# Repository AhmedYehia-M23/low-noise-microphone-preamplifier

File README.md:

# Low-Noise Electret Microphone Preamplifier

A 5 V single-supply electret microphone preamplifier designed in KiCad 10. The production PCB uses an **Analog Devices AD8656ARMZ** dual op-amp (MSOP-8), adjustable non-inverting gain targeting approximately **30–40 dB**, and RC high-pass and low-pass filtering.

**Status:** PCB design finalized and released for fabrication; assembly and bench testing remain pending. The repository contains user-run **AD8656 LTspice simulations** and separately archived results from an earlier OPA165x-based revision.

## Project files

- [PCB assembly BOM](hardware/BOM.md) ([CSV](hardware/BOM.csv))
- [Editable KiCad schematic](hardware/kicad/Microphone.kicad_sch)
- [Editable KiCad PCB](hardware/kicad/Microphone.kicad_pcb)
- [KiCad project settings](hardware/kicad/Microphone.kicad_pro)
- [AD8656 LTspice schematic](simulation/ltspice/Microphone_Preamplifier_AD8656.asc)
- [Earlier OPA165x LTspice schematic](simulation/ltspice/Microphone_Preamplifier_OPA165x.asc)
- [LTspice setup notes](simulation/ltspice/README.md)
- [Noise analysis notes](docs/noise-analysis.md) — resistor noise estimates and final-device measurement plan

## Project status

| Stage | Status |
| --- | --- |
| Circuit and PCB design | Complete |
| KiCad DRC | **0 errors, 0 warnings, 0 unconnected items, 0 schematic parity violations** on the final local design |
| PCB fabrication | Design released for fabrication |
| PCB assembly | Pending; components will be soldered by hand |
| LTspice analyses | Passed for the earlier OPA165x-based simulation |
| AD8656 simulation | User-run AC, transient and noise results documented; not independently rerun |
| Bench gain, bandwidth, noise and supply-current measurements | Pending |

The files in `hardware/kicad/` are the final production-source revision. Gerbers and drill exports are not included in this repository.

## Hardware specifications

| Parameter | Final design |
| --- | --- |
| Supply | 5 V DC |
| Microphone | EKULIT EMY-6027P/N-R-42 electret capsule |
| Op-amp | **AD8656ARMZ** (dual, MSOP-8; KiCad value `AD8656`) |
| Gain | Adjustable; nominal target approximately 30–40 dB |
| High-pass network | 100 nF / 47 kΩ; nominal corner approximately 33.9 Hz |
| Low-pass network | 330 Ω / 27 nF; nominal corner approximately 17.9 kHz |
| Power switch | SPDT slide switch, SS ESP101 / ESP1010 footprint |
| Power indicator | Green 1206 LED (`D1`) and 2.2 kΩ series resistor (`R9`) |
| PCB | 2 layers, approximately 60.06 × 40.03 mm, 1.6 mm FR-4, 1 oz copper |
| Layout | Bottom-layer GND plane, 0603 passives, through-hole connectors and test points |

The nominal RC corner frequencies are **component-value calculations**, not measured bandwidth for the AD8656 hardware.

## Signal path

**Electret microphone → bias / AC coupling → AD8656 non-inverting gain stage → RC low-pass filter → output coupling → audio output**

The other amplifier in the dual AD8656 buffers the mid-supply reference.

### Microphone input

The electret capsule is biased through **R3 = 2.2 kΩ**. The microphone signal passes through **C4 = 100 nF** into the amplifier input network; **R4 = 47 kΩ** sets the nominal high-pass corner.

```text
f_HP = 1 / (2π × 47 kΩ × 100 nF) ≈ 33.9 Hz
```

The microphone's project-local footprint is in `hardware/kicad/AudioPreamp.pretty/`.

### Mid-supply reference

A **10 kΩ / 10 kΩ** divider (`R1`, `R2`) derives approximately **2.5 V** from the 5 V supply. **C3 = 10 µF** filters the divider node; the second AD8656 channel buffers it as `VREF`.

### Variable gain

The non-inverting amplifier uses:

- **R5 = 22 kΩ**
- **R6 = 220 Ω**
- **RV1 = 500 Ω** adjustable potentiometer

The idealized gain is:

$$
A_v = 1 + \frac{R_5}{R_6 + R_{V1}}
$$

The gain-setting network targets approximately **30–40 dB**, depending on the potentiometer setting. This is a **design target**, not a measured AD8656 gain result.

### Low-pass and output coupling

**R7 = 330 Ω** and **C5 = 27 nF** form the nominal low-pass filter:

```text
f_LP = 1 / (2π × 330 Ω × 27 nF) ≈ 17.9 kHz
```

**C6 = 4.7 µF** AC-couples the signal to `AUDIO_OUT`; **R8 = 100 kΩ** provides a DC reference at the output.

### Power input and indication

The incoming **5 V** supply is controlled by the on-board **SPDT slide switch (`SW1`)**. A **green 1206 LED (`D1`)** with a **2.2 kΩ series resistor (`R9`)** indicates power.

Power bypassing uses **C1 = 100 nF** and **C2 = 10 µF**; the reference divider is filtered with **C3 = 10 µF**.

## PCB design

The two-layer board includes:

- AD8656 in **MSOP-8, 0.65 mm pitch**
- 0603 resistor/capacitor footprints and a 1206 power LED
- Through-hole electret microphone and adjustable potentiometer
- Screw-terminal connections for power and audio output
- Through-hole SPDT power switch, using the project-local `SW_ESP1010_SPDT_Vertical` footprint
- Bottom-layer ground plane
- Test points for `VREF`, `AMP_OUT`, `LPF_OUT`, `AUDIO_OUT` and GND

The final board was checked in KiCad with **zero DRC errors, warnings, unconnected items and schematic-parity violations** before manufacturing export.

### KiCad schematic

[View the full-resolution schematic](docs/kicad/Microphone.svg)

The editable KiCad source files above contain the final PCB revision. The 3D previews show the final PCB layout; footprints without an associated 3D component model may appear unpopulated.

### Routed PCB layout

### Angled 3D view

## LTspice simulations

### 1 kHz transient response

*AD8656 LTspice transient simulation at 1 kHz (`Rpot=1 Ω`, `I1 = SINE(250u 1u 1k)`). Separate scales show approximately 4.2 mVpp input (`V(VBIAS,VREF)`) and 420 mVpp output (`V(AUDIO_OUT)`), corresponding to approximately 100 V/V (40 dB) simulated gain. The plot does not establish measured hardware performance or total harmonic distortion.*

### AC amplifier-stage gain — maximum setting

*User-run LTspice AC analysis with `Rpot=1 Ω`. Trace: `V(n001,vref)/V(vbias,vref)`, displayed by LTspice in dB. The simulated gain at 1 kHz is approximately **40.05 dB**, consistent with `1 + 22 kΩ / (220 Ω + 1 Ω)`. This is amplifier-stage gain, not the complete microphone-to-output frequency response or a physical measurement.*

### Full signal-path frequency response — 30 dB setting

*User-run LTspice AC sweep with `Rpot=500 Ω`. Trace: `V(audio_out)/V(mic_out)`, shown in dB. The plot shows a band-pass response with approximately **30 dB midband gain**, including both the low- and high-frequency roll-offs. At the 1 kHz gain of **29.5233 dB**, the user-run `.meas AC` results place the approximately −3 dB threshold at **26.5132 dB**, crossing at **30.8214 Hz** and **19,702.8 Hz (19.70 kHz)**. These cutoffs are relative to the 1 kHz gain, not necessarily the absolute passband peak. This is simulated, not hardware-measured, performance.*

### Stepped AC response — adjustable gain

*User-run LTspice AC analysis with `.step param Rpot list 1 179 500`. The green, blue, and red solid curves correspond to approximately **40 dB (1 Ω)**, **35 dB (179 Ω)**, and **30 dB (500 Ω)** midband gain, respectively. Dotted curves show phase; this is the simulated full signal-path response (`V(audio_out)/V(mic_out)`), not physical measurement data.*

### Stepped transient response — three gain settings

*User-run 1 kHz LTspice transient simulation with `I1 = SINE(250u 1u 1k)` and `.step param Rpot list 1 179 500`. The green (1 Ω), blue (179 Ω), and red (500 Ω) traces show approximately **420 mVpp**, **235 mVpp**, and **130 mVpp** at `V(audio_out)`, respectively. Values are approximate readings from the screenshot, not calibrated measurements or distortion results.*

The [AD8656 simulation schematic](simulation/ltspice/Microphone_Preamplifier_AD8656.asc) contains the revised op-amp stages, a **1 kHz sine-wave stimulus** and a clean default **30 dB AC sweep** with gain and cutoff-frequency measurements. Other analysis configurations are documented in the [LTspice setup notes](simulation/ltspice/README.md). It references the external `ad8656.cir` model. The vendor model is not included in the repository. The plots here document user-run LTspice simulations, not independently repeated simulations or physical measurements. The switch and LED are not represented in this analog signal-path simulation.

The [earlier OPA165x schematic](simulation/ltspice/Microphone_Preamplifier_OPA165x.asc) is retained as a record of the original analog-stage development. Its results are historical and must not be attributed to the final AD8656 design.

The previous model passed:

- Operating-point analysis (`.op`)
- Transient analysis
- Stepped transient analysis
- Stepped AC analysis

Previously simulated gain points were approximately **30 / 35 / 40 dB**. At the ~30 dB setting, the previous model showed approximate −3 dB frequencies of **33.9 Hz and 17.8 kHz**. **These are historical OPA165x-model results, not validated AD8656 performance.**

The original results are retained in [`simulation/ltspice/`](simulation/ltspice/) and the repository history, not as current hardware validation.

## Noise and measurement plan

### Simulated output-noise spectral density — 30 dB setting

*User-run LTspice `.noise V(audio_out) I1 dec 100 20 20k` analysis with `Rpot=500 Ω`. The plotted `V(onoise)` is output-noise **amplitude spectral density** in V/√Hz over 20 Hz–20 kHz. It represents the circuit and SPICE model as configured, with an idealized microphone current-source stimulus; it does **not** include the real electret capsule's complete self-noise, and is not itself an integrated RMS noise figure or hardware measurement.*

**Integrated simulated output noise (20 Hz–20 kHz): 31.88 µV RMS**, using `Rpot=500 Ω`. The user-reported LTspice measurement was `.meas NOISE Output_Noise_RMS INTEG V(onoise) FROM=20 TO=20k`, returning `3.18777e-05 V RMS`. This is a simulation result from the configured circuit and AD8656 macro-model, **not a measurement of the real microphone or assembled PCB**.

The final AD8656 implementation has **no published measured noise figure**. Device-level noise specifications and resistor thermal-noise estimates should not be presented as total system noise. The [noise analysis notes](docs/noise-analysis.md) distinguish the earlier OPA1652 reference values from the AD8656 hardware and outline the planned measurements.

After assembly, the planned checks are:

1. Power-rail voltage, polarity, reference voltage and supply current
2. Correct power-switch and LED operation
3. Signal-chain continuity and adjustable gain
4. Frequency response, output swing and clipping
5. Output noise and sensitivity to supply/interference conditions

No bench-tested gain, noise or bandwidth claims are made yet.

## Repository layout

```text
.
├── README.md
├── .gitignore
├── .gitattributes
├── hardware/
│   ├── BOM.md
│   ├── BOM.csv
│   └── kicad/
│       ├── Microphone.kicad_pro
│       ├── Microphone.kicad_sch
│       ├── Microphone.kicad_pcb
│       ├── fp-lib-table
│       └── AudioPreamp.pretty/
│           ├── Microphone_EKULIT_EMY-6027PNR-42.kicad_mod
│           └── SW_ESP1010_SPDT_Vertical.kicad_mod
├── simulation/
│   └── ltspice/
│       ├── Microphone_Preamplifier_AD8656.asc
│       ├── Microphone_Preamplifier_OPA165x.asc
│       └── README.md
└── docs/
    ├── noise-analysis.md
    ├── kicad/
    └── ltspice/
```

## Third-party attribution

- **Analog Devices, Inc.** — manufacturer of the AD8656 operational amplifier and copyright holder of the AD8656 SPICE macro-model (© 2010, 2012 Analog Devices, Inc.). See the [official AD8656 product page](https://www.analog.com/en/products/ad8656.html) for the datasheet and model.
- The Analog Devices SPICE macro-model is **not redistributed** in this repository. It is subject to [Analog Devices' SPICE model license](https://www.analog.com/en/license/spice-models.html); users must obtain it directly from the manufacturer and follow the applicable terms.
- This is an independent electronics project and is **not affiliated with or endorsed by Analog Devices**.

## Open the project

1. Install KiCad 10 (or a compatible newer version).
2. Download or clone this repository.
3. Open `hardware/kicad/Microphone.kicad_pro`.

The microphone and power-switch footprints are stored locally and referenced through the `AudioPreamp.pretty` footprint library. Standard symbols, footprints and 3D models come from the normal KiCad installation.

Temporary backups, KiCad caches, generated manufacturing exports and LTspice waveform files are intentionally excluded from Git.

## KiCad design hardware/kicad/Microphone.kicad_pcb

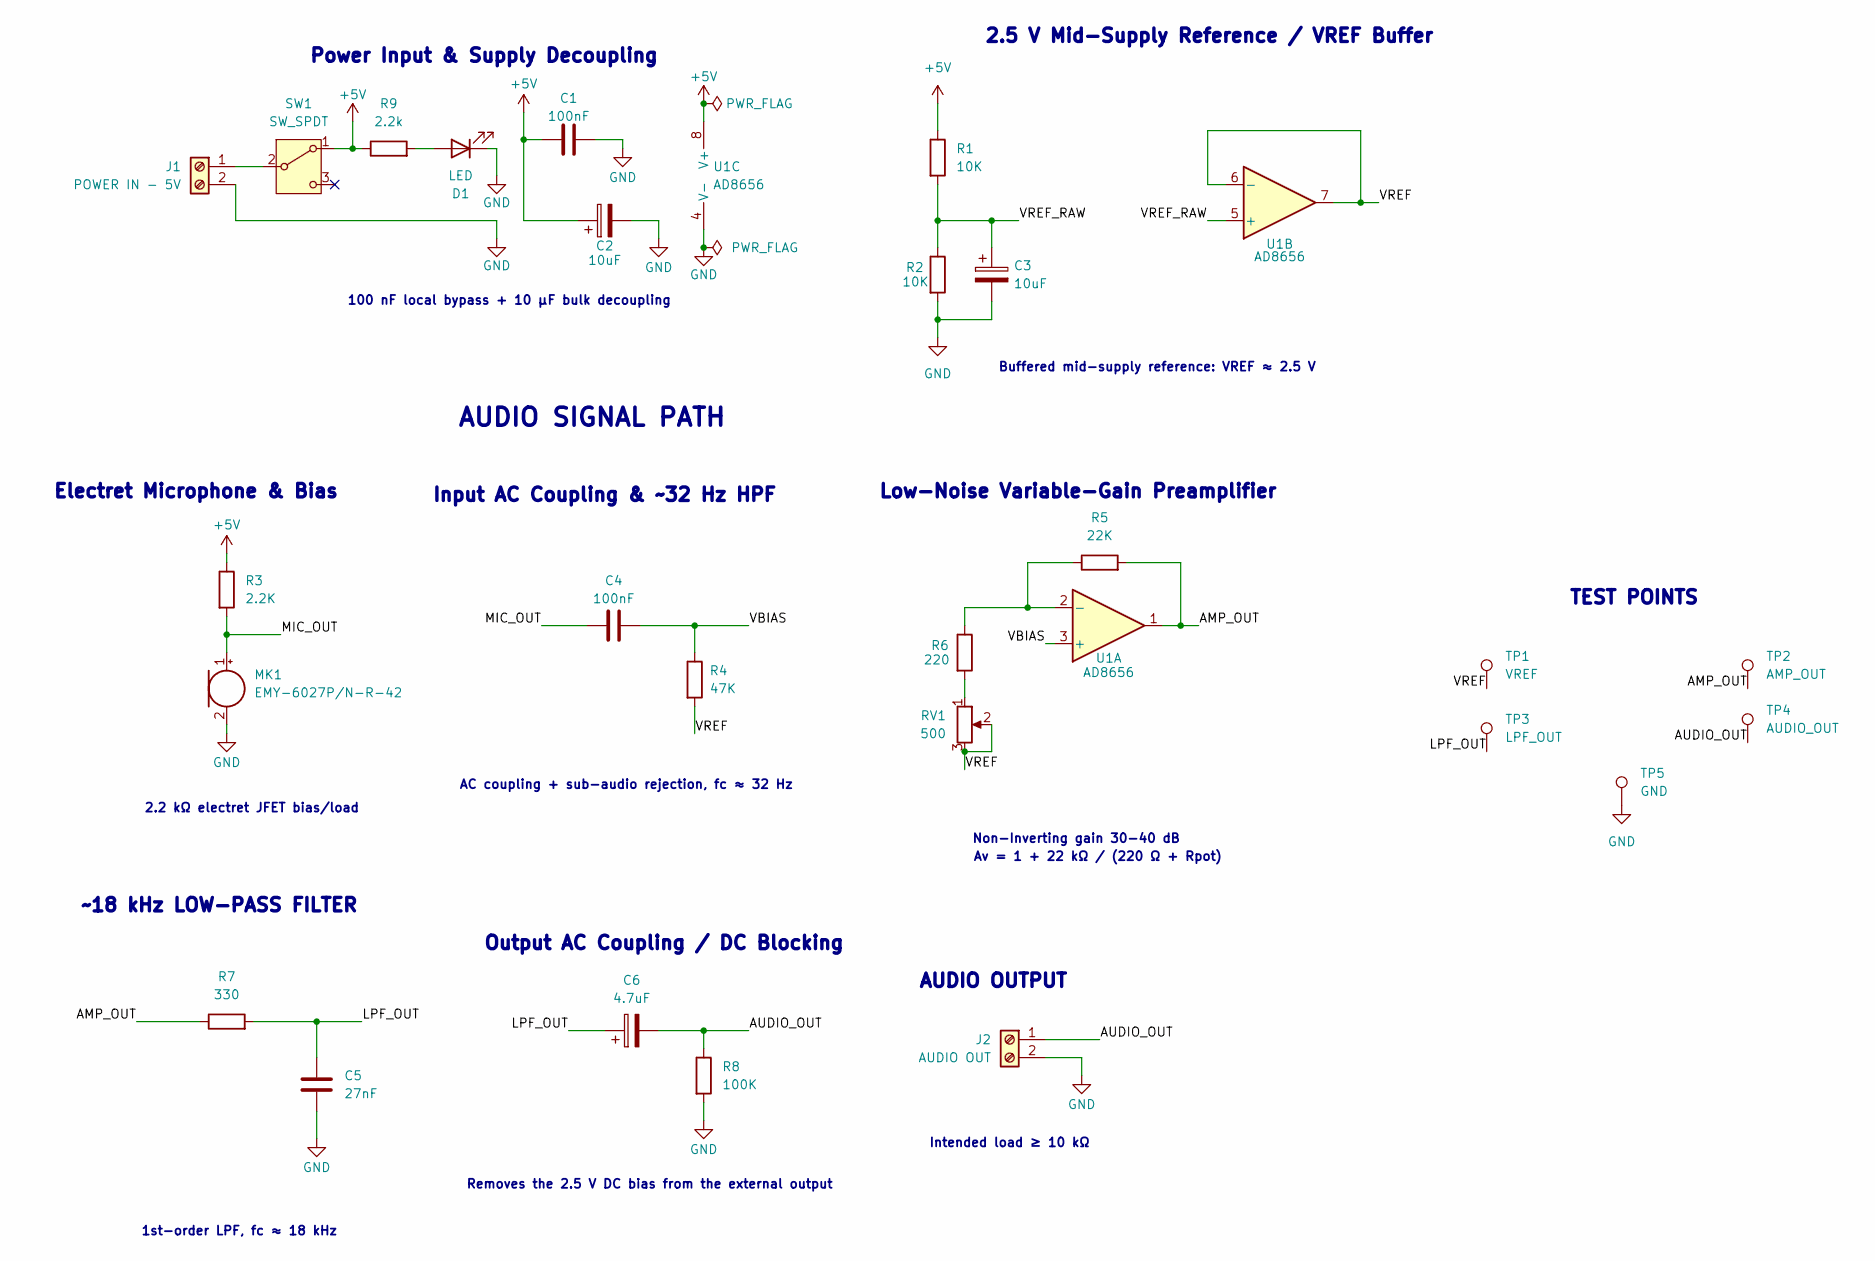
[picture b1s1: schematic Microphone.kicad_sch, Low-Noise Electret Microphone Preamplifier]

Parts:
C1, C4: 100nF; C_0603_1608Metric_Pad1.08x0.95mm_HandSolder
C2, C3: 10uF; CP_Elec_5x5.4
C5: 27nF; C_0603_1608Metric_Pad1.08x0.95mm_HandSolder
C6: 4.7uF; CP_Elec_4x5.8
D1: LED; LED_1206_3216Metric
J1: POWER IN - 5V; TerminalBlock_Phoenix_MKDS-1,5-2-5.08_1x02_P5.08mm_Horizont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
J2: AUDIO OUT; TerminalBlock_Phoenix_MKDS-1,5-2-5.08_1x02_P5.08mm_Horizont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
MK1: EMY-6027P/N-R-42; Microphone_EKULIT_EMY-6027PNR-42
R1, R2: 10K; R_0603_1608Metric_Pad0.98x0.95mm_HandSolder
R3: 2.2K; R_0603_1608Metric_Pad0.98x0.95mm_HandSolder
R4: 47K; R_0603_1608Metric_Pad0.98x0.95mm_HandSolder
R5: 22K; R_0603_1608Metric_Pad0.98x0.95mm_HandSolder
R6: 220; R_0603_1608Metric_Pad0.98x0.95mm_HandSolder
R7: 330; R_0603_1608Metric_Pad0.98x0.95mm_HandSolder
R8: 100K; R_0603_1608Metric_Pad0.98x0.95mm_HandSolder
R9: 2.2k; R_0603_1608Metric_Pad0.98x0.95mm_HandSolder
RV1: 500; Potentiometer_Piher_PT-10-H01_Horizontal
SW1: SW_SPDT; SW_ESP1010_SPDT_Vertical
TP1: VREF; TestPoint_THTPad_D2.0mm_Drill1.0mm
TP2: AMP_OUT; TestPoint_THTPad_D2.0mm_Drill1.0mm
TP3: LPF_OUT; TestPoint_THTPad_D2.0mm_Drill1.0mm
TP4: AUDIO_OUT; TestPoint_THTPad_D2.0mm_Drill1.0mm
TP5: GND; TestPoint_THTPad_D2.0mm_Drill1.0mm
U1: AD8656; MSOP-8_3x3mm_P0.65mm

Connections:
+5V: C1.1, C2.1, R1.1, R3.1, R9.1, SW1.1 (A), U1.8 (V+)
/AMP_OUT: R5.2, R7.1, TP2.1 (1_1), U1.1
/AUDIO_OUT: C6.2, J2.1, R8.1, TP4.1 (1_1)
/LPF_OUT: C5.1, C6.1, R7.2, TP3.1 (1_1)
/MIC_OUT: C4.2, MK1.1 (+), R3.2
/VBIAS: C4.1, R4.1, U1.3 (+)
/VREF: R4.2, RV1.2, RV1.3, TP1.1 (1_1), U1.6 (-), U1.7
/VREF_RAW: C3.1, R1.2, R2.1, U1.5 (+)
GND: C1.2, C2.2, C3.2, C5.2, D1.1 (K), J1.2, J2.2, MK1.2 (-), R2.2, R8.2, TP5.1 (1_1), U1.4 (V-)
unnamed: D1.2 (A), R9.2
unnamed: J1.1, SW1.2 (B)
unnamed: R6.2, RV1.1
unnamed: R5.1, R6.1, U1.2 (-)

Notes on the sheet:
AUDIO SIGNAL PATH
1st-order LPF, fc ≈ 18 kHz
AC coupling + sub-audio rejection, fc ≈ 32 Hz
100 nF local bypass + 10 µF bulk decoupling
Low-Noise Variable-Gain Preamplifier
Input AC Coupling & ~32 Hz HPF
Non-Inverting gain 30-40 dB
Buffered mid-supply reference: VREF ≈ 2.5 V
2.5 V Mid-Supply Reference / VREF Buffer
Output AC Coupling / DC Blocking
Electret Microphone & Bias
TEST POINTS
2.2 kΩ electret JFET bias/load
Power Input & Supply Decoupling
AUDIO OUTPUT
Intended load ≥ 10 kΩ
~18 kHz LOW-PASS FILTER
Av = 1 + 22 kΩ / (220 Ω + Rpot)
Removes the 2.5 V DC bias from the external output

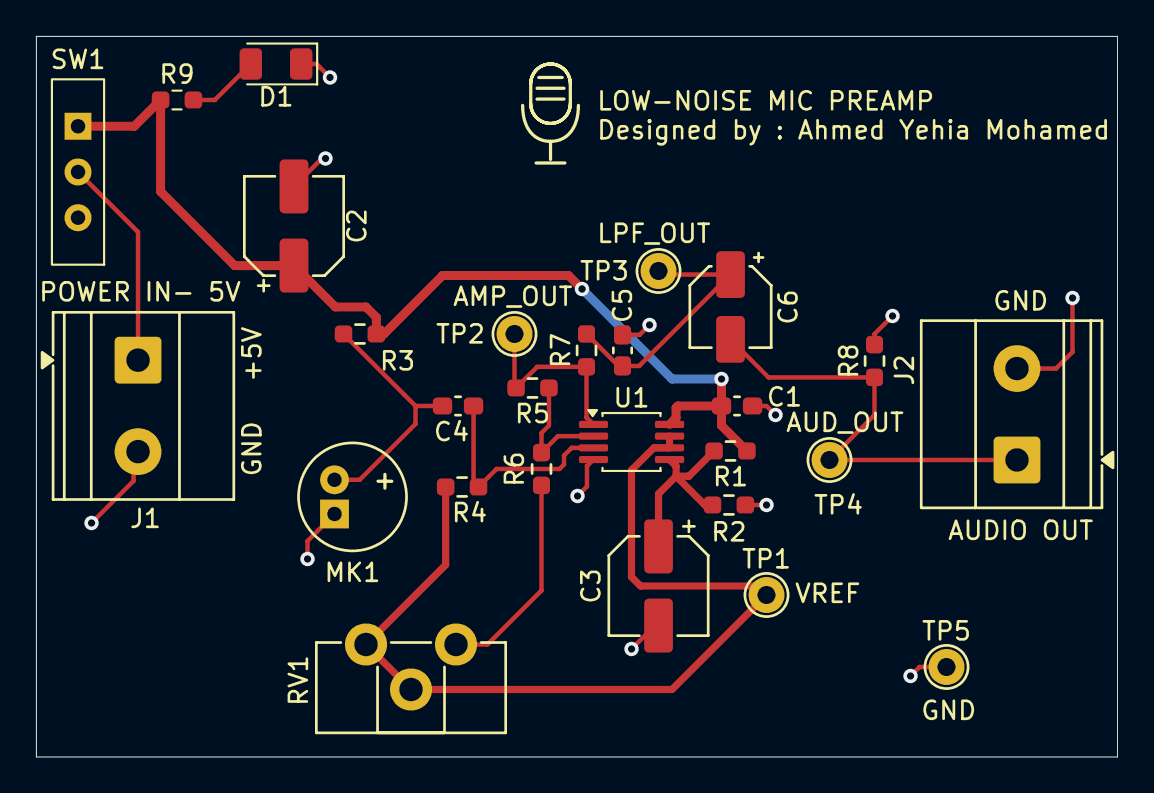
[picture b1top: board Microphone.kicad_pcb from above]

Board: 2 copper layers, 60.1 x 40.0 mm, 27 parts (0 on the bottom side), 13 nets.

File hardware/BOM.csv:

Category,References,Quantity,Value / specification,KiCad footprint,Function,Assembly / verification notes
Resistor,R1 R2,2,10 kΩ,Resistor_SMD:R_0603_1608Metric_Pad0.98x0.95mm_HandSolder,Mid-supply divider,0603; tolerance and power rating not specified in KiCad
Resistor,R3 R9,2,2.2 kΩ,Resistor_SMD:R_0603_1608Metric_Pad0.98x0.95mm_HandSolder,Microphone bias and LED limiting,0603; R9 is the LED series resistor
Resistor,R4,1,47 kΩ,Resistor_SMD:R_0603_1608Metric_Pad0.98x0.95mm_HandSolder,Amplifier input bias,0603
Resistor,R5,1,22 kΩ,Resistor_SMD:R_0603_1608Metric_Pad0.98x0.95mm_HandSolder,Gain feedback,0603
Resistor,R6,1,220 Ω,Resistor_SMD:R_0603_1608Metric_Pad0.98x0.95mm_HandSolder,Gain-setting resistor,0603
Resistor,R7,1,330 Ω,Resistor_SMD:R_0603_1608Metric_Pad0.98x0.95mm_HandSolder,Low-pass series resistor,0603
Resistor,R8,1,100 kΩ,Resistor_SMD:R_0603_1608Metric_Pad0.98x0.95mm_HandSolder,Output reference / load resistor,0603
Capacitor,C1 C4,2,100 nF,Capacitor_SMD:C_0603_1608Metric_Pad1.08x0.95mm_HandSolder,Supply bypass and microphone AC coupling,0603 non-polarized; voltage rating unspecified
Capacitor,C2 C3,2,10 µF,Capacitor_SMD:CP_Elec_5x5.4,Supply bulk and VREF_RAW filtering,"Polarized SMD electrolytic; verify positive/negative orientation, can size and voltage rating"
Capacitor,C5,1,27 nF,Capacitor_SMD:C_0603_1608Metric_Pad1.08x0.95mm_HandSolder,Low-pass shunt capacitor,0603 non-polarized
Capacitor,C6,1,4.7 µF,Capacitor_SMD:CP_Elec_4x5.8,AC-coupled output capacitor,"Polarized SMD electrolytic; verify positive/negative orientation, can size and voltage rating"
Diode,D1,1,LED,LED_SMD:LED_1206_3216Metric,Power-on indicator,1206; green intended; schematic does not specify color; check polarity
Connector,J1 J2,2,2-position terminal block; 5.08 mm pitch,"TerminalBlock_Phoenix:TerminalBlock_Phoenix_MKDS-1,5-2-5.08_1x02_P5.08mm_Horizontal",5 V power input and audio output,Horizontal through-hole; check mating wire and mechanical fit
Microphone,MK1,1,EMY-6027P/N-R-42 electret microphone,AudioPreamp:Microphone_EKULIT_EMY-6027PNR-42,Electret capsule,Custom through-hole footprint; check capsule pin polarity and diameter
Potentiometer,RV1,1,500 Ω,Potentiometer_THT:Potentiometer_Piher_PT-10-H01_Horizontal,Variable gain control,Through-hole horizontal; confirm exact footprint fit and wiper pinout; NOT 500 kΩ
Switch,SW1,1,SPDT slide switch,AudioPreamp:SW_ESP1010_SPDT_Vertical,5 V power switch,3-pin vertical through-hole; pin 3 deliberately unused; confirm mechanical fit and switch action
Integrated circuit,U1,1,AD8656ARMZ; dual operational amplifier,Package_SO:MSOP-8_3x3mm_P0.65mm,Main gain stage and VREF buffer,"One MSOP-8 dual op-amp IC, not two chips; verify device orientation"
